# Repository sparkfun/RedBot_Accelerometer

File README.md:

RedBot Accelerometer
==================

[*SparkFun RedBot Accelerometer*](https://www.sparkfun.com/products/12589)

The accelerometer sensor is an add-on for the RedBot kit that provides bump and motion detection. 
It is an I<sup>2</sup>C, and is a 3-axis sensor.

Repository Contents
-------------------

* **/Hardware** - Eagle PCB layout files
* **/Production** - Pogo testbed files

Documentation
-------------------
* **[Assembly Guide for RedBot with Shadow Chassis](https://learn.sparkfun.com/tutorials/assembly-guide-for-redbot-with-shadow-chassis)**
* **[Experiment Guide for RedBot with Shadow Chassis](https://learn.sparkfun.com/tutorials/experiment-guide-for-redbot-with-shadow-chassis)**

License Information
-------------------

The hardware is released under [Creative Commons ShareAlike 4.0 International](https://creativecommons.org/licenses/by-sa/4.0/).
The code is beerware; if you see me (or any other SparkFun employee) at the local, and you've found our code helpful, please buy us a round!

Distributed as-is; no warranty is given.

Authors: Mike Hord @ SparkFun Electonics

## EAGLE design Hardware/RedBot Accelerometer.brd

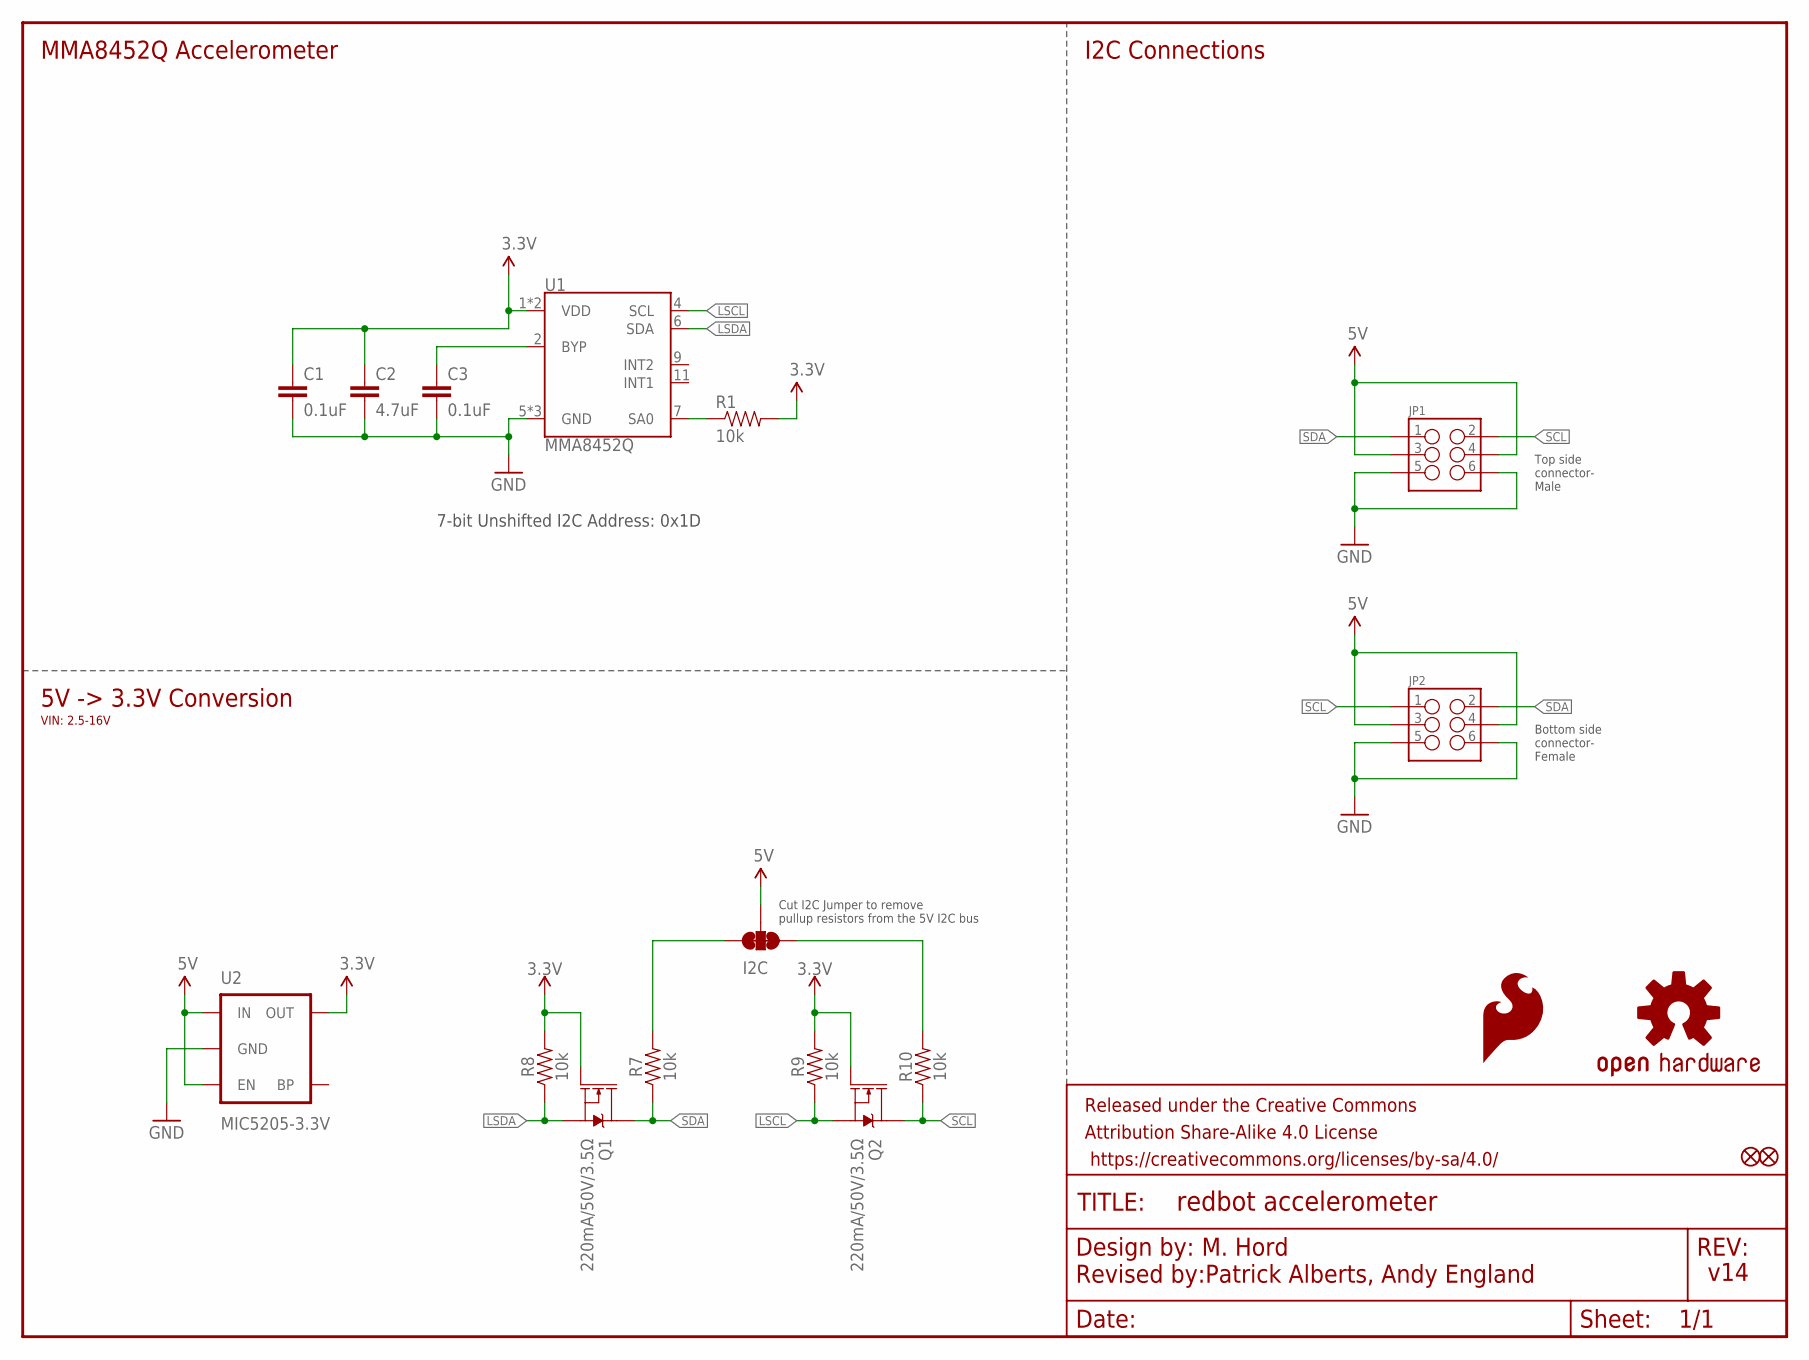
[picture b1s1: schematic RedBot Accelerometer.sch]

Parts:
C1, C3: 0.1uF; 0603
C2: 4.7uF; 0603
FID1, FID3: FIDUCIAL1X2; FIDUCIAL-1X2
FRAME1: FRAME-LETTER; CREATIVE_COMMONS
I2C: JUMPER-SMT_3_2-NC_TRACE_SILK; SMT-JUMPER_3_2-NC_TRACE_SILK
JP1: M03X2SMT; 2X3_SMT_POSTS
JP2: M03X2FEMALE_SMD; 2X3_SMD
LOGO2: OSHW-LOGOS; OSHW-LOGO-S
LOGO4: SFE_LOGO_FLAME.1_INCH; SFE_LOGO_FLAME_.1
Q1, Q2: 220mA/50V/3.5Ω; SOT23-3
R1, R7, R8, R9, R10: 10k; 0603
U1: MMA8452Q; QFN-16
U2: MIC5205-3.3V; SOT23-5

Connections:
3.3V: C1.1, C2.1, Q1.1 (G), Q2.1 (G), R1.2, R8.2, R9.2, U1.1 (VDD), U1.14 (VDD), U2.5 (OUT)
5V: I2C.2, JP1.3, JP1.4, JP2.3, JP2.4, U2.1 (IN), U2.3 (EN)
ADDR: R1.1, U1.7 (SA0)
GND: C1.2, C2.2, C3.2, JP1.5, JP1.6, JP2.5, JP2.6, U1.5 (GND), U1.10 (GND), U1.12 (GND), U2.2 (GND)
LSCL: Q2.2 (S), R9.1, U1.4 (SCL)
LSDA: Q1.2 (S), R8.1, U1.6 (SDA)
unnamed: C3.1, U1.2 (BYP)
unnamed: I2C.3, R7.2
unnamed: I2C.1, R10.2
SCL: JP1.2, JP2.1, Q2.3 (D), R10.1
SDA: JP1.1, JP2.2, Q1.3 (D), R7.1

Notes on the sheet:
v14
M. Hord
Top side connector- Male
Bottom side connector- Female
Revised by:Patrick Alberts, Andy England
Cut I2C Jumper to remove pullup resistors from the 5V I2C bus
5V -> 3.3V Conversion
MMA8452Q Accelerometer
I2C Connections
VIN: 2.5-16V
7-bit Unshifted I2C Address: 0x1D

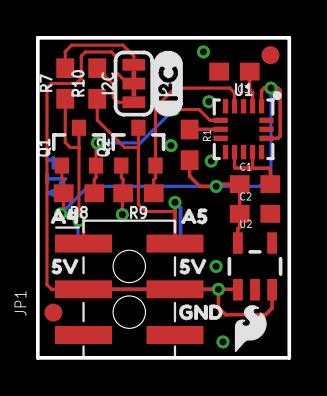
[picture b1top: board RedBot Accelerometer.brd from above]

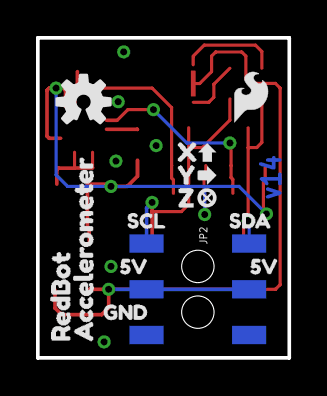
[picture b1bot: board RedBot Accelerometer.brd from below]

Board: 2 copper layers, 14.0 x 17.8 mm, 39 parts (15 on the bottom side), 11 nets.

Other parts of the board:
LOGO3: LOGO-SFESK; SFE-LOGO-FLAME
U$1: X0
U$2: A42
U$3: A53
U$4, U$5, U$8, U$11: _5V1
U$6, U$7: GND0
U$9: SDA6
U$10: _SCL7
U$12: ##3
U$13: ##4
U$14: Y1
U$15: Z2
U$16: REDBOT4
U$17: ACCELEROMETER5
U$19: I2C

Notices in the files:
parts and their libraries:
SparkFun-Aesthetics: Licensing: CC v3.0 Share-Alike You are welcome to use this library for commercial purposes.
SparkFun-Aesthetics: Released under the Creative Commons Attribution Share-Alike 4.0 License
SparkFun-Aesthetics: Released under the Creative Commons
